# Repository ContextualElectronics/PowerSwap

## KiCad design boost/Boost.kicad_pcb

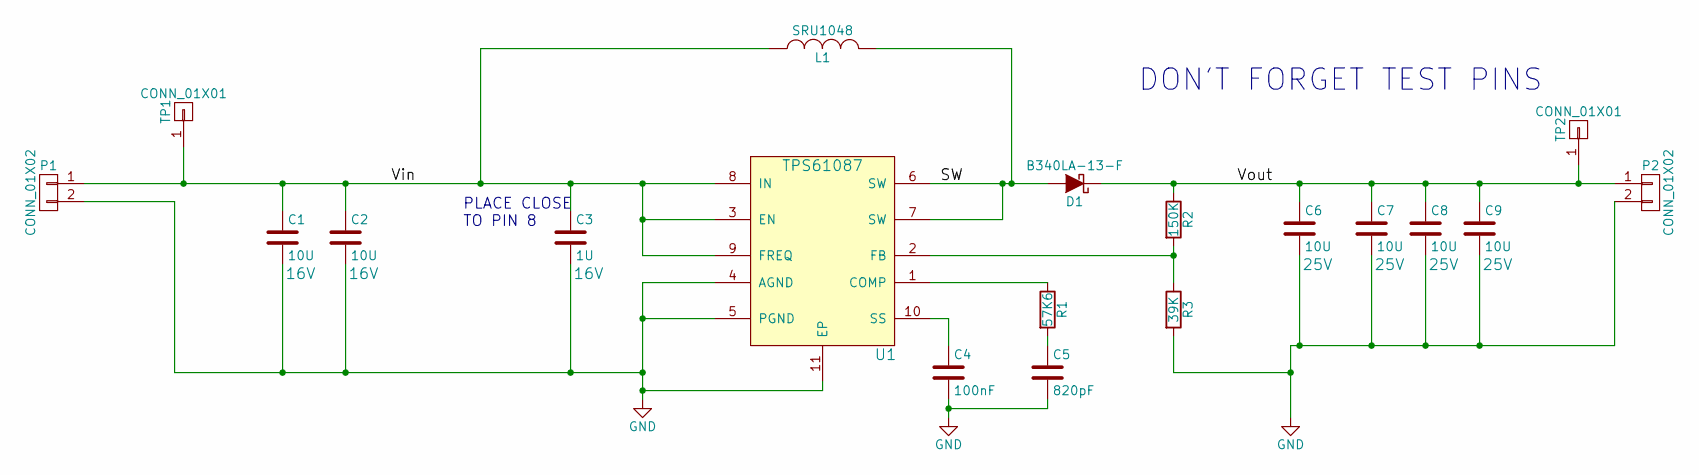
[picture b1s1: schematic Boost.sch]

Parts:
C1, C2: 10U; C_1206_HandSoldering; Voltage 16V
C3: 1U; C_0805_HandSoldering; Voltage 16V
C4: 100nF; C_0805_HandSoldering
C5: 820pF; C_0805_HandSoldering
C6, C7, C8, C9: 10U; C_1206_HandSoldering; Voltage 25V
D1: B340LA-13-F; SMA-SMB_Universal_Handsoldering; MPN B340LA-13-F
L1: SRU1048; MPN SRU1048-4R7Y
P1, P2: CONN_01X02; Pin_Header_Straight_1x02
R1: 57K6; R_0805_HandSoldering
R2: 150K; R_0805_HandSoldering
R3: 39K; R_0805_HandSoldering
TP1, TP2: CONN_01X01; Measurement_Point_Square-SMD-Pad_Big
U1: TPS61087; MPN TPS61087QDRCRQ1

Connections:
/SW: D1.2 (A), L1.2, U1.6 (SW), U1.7 (SW)
/Vin: C1.1, C2.1, C3.1, L1.1, P1.1, TP1.1, U1.3 (EN), U1.8 (IN), U1.9 (FREQ)
/Vout: C6.1, C7.1, C8.1, C9.1, D1.1 (K), P2.1, R2.1, TP2.1; also elsewhere on the board
GND: C1.2, C2.2, C3.2, C4.2, C5.2, C6.2, C7.2, C8.2, C9.2, P1.2, P2.2, R3.2, U1.4 (AGND), U1.5 (PGND), U1.11 (EP); also elsewhere on the board
unnamed: C4.1, U1.10 (SS)
unnamed: C5.1, R1.2
unnamed: R1.1, U1.1 (COMP)
unnamed: R2.2, R3.1, U1.2 (FB)

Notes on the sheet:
PLACE CLOSE TO PIN 8
DON'T FORGET TEST PINS

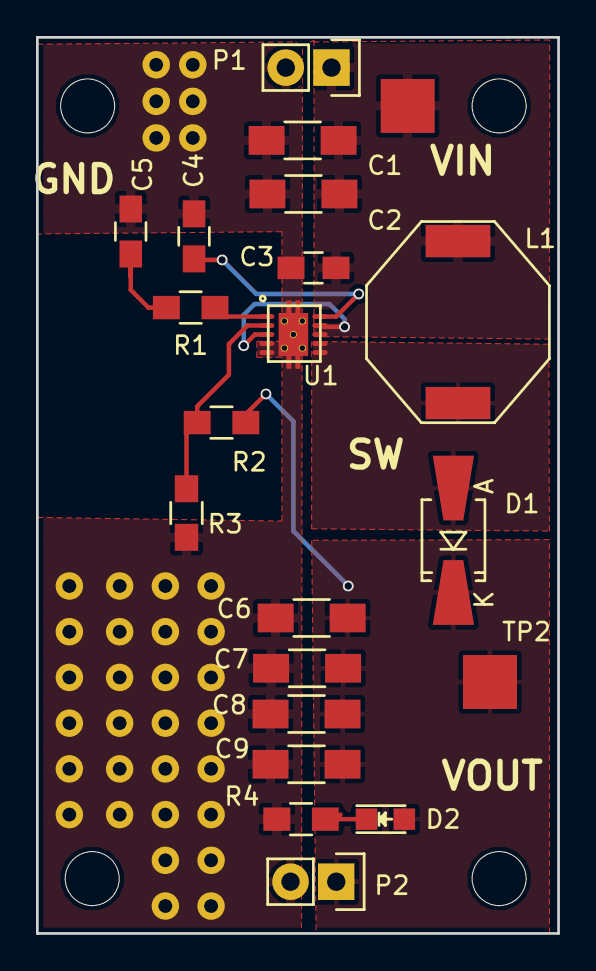
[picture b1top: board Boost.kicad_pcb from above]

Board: 2 copper layers, 29.0 x 49.8 mm, 21 parts (0 on the bottom side), 9 nets.

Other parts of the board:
D2: LED; LED-0805
R4: 500; R_0805_HandSoldering

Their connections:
/Vout: D2.2; also elsewhere on the board
GND: R4.2; also elsewhere on the board
unnamed: D2.1, R4.1

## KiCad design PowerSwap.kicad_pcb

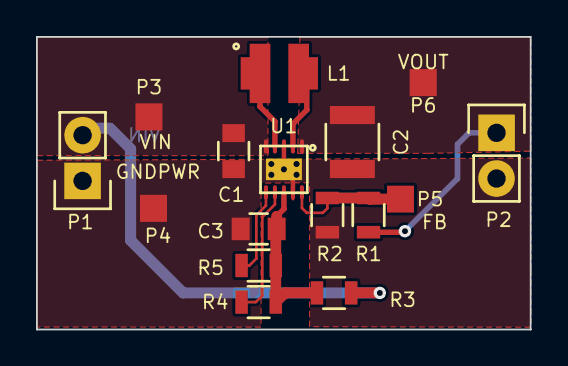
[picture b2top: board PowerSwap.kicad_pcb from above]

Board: 2 copper layers, 27.4 x 16.3 mm, 16 parts (0 on the bottom side), 9 nets.

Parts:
C1: 4.7UF; C_0805
C2: 22UF; C_1210
C3: 0.1UF; C_0805
L1: 2.2uH; LQH3NPN2R2MM0L
P1, P2: CONN_01X02; Pin_Header_Straight_1x02
P3, P4, P5, P6: TST; Measurement_Point_Square-SMD-Pad_Small
R1: 1.2M; R_0805
R2: 215K; R_0805
R3, R4, R5: 0; R_0805
U1: TPS63030

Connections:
/FB: P5.1, R1.2, R2.1, U1.10
/VIN: C1.1, P1.2, P3.1, R3.2, U1.5
/VINA: C3.1, R3.1, R4.2, R5.2, U1.8
/VOUT: C2.1, P2.1, P6.1, R1.1, U1.1
GNDPWR: C1.2, C2.2, C3.2, P1.1, P2.2, P4.1, R2.2, U1.3, U1.9, U1.11
unnamed: L1.1, U1.4
unnamed: L1.2, U1.2
unnamed: R4.1, U1.7
unnamed: R5.1, U1.6

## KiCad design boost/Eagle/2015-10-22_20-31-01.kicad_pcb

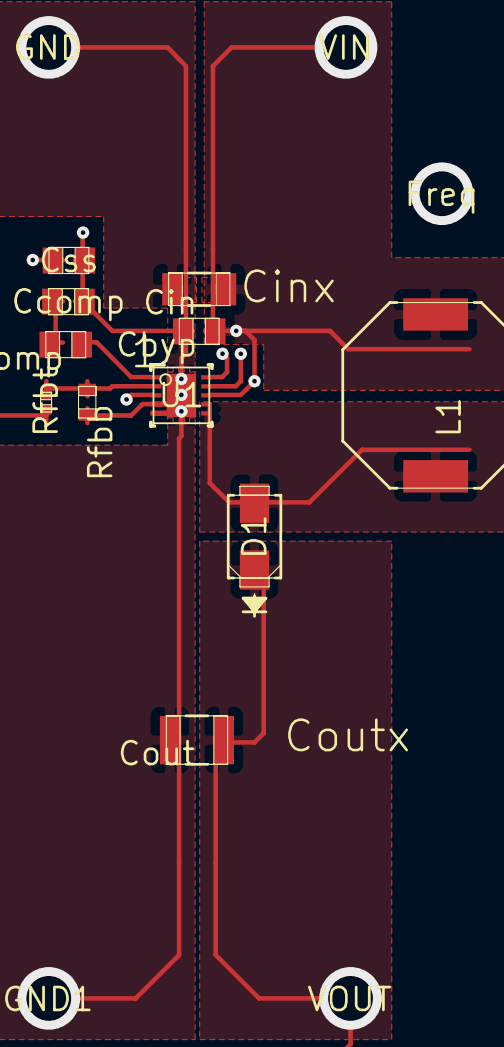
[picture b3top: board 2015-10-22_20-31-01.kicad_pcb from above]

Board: 10 copper layers, 16 parts (0 on the bottom side), 9 nets.

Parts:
Cbyp: 0805
Ccomp: 0805
Cin: 1206
Cout: 1210
Css: 0805
D1: SMA
Freq: TP-1502
GND, GND1: TP-1502
L1: SRU1048
Rcomp: 0805
Rfbb: 0603
Rfbt: 0402
U1: DRC0010A
VIN: TP-1502
VOUT: TP-1502

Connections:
0: Cbyp.2, Ccomp.2, Cin.2, Cout.2, Css.2, GND.1, GND1.1, Rfbb.2, U1.4, U1.5, U1.11
1: Cbyp.1, Cin.1, L1.1, U1.3, U1.8, VIN.1
2: Cout.1, D1.1, Rfbt.1, VOUT.1
4: D1.2, L1.2, U1.6, U1.7
5: Rcomp.1, U1.1
6: Rfbb.1, Rfbt.2, U1.2
7: Ccomp.1, Rcomp.2
13: Freq.1, U1.9
14: Css.1, U1.10

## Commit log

2015-08-01 Added TPS63030 component plus passives
2015-08-09 Added values to schematic and added inductor footprint
2015-08-09 Added TPS63030 Footprint
2015-08-09 Imported footprints
2015-08-10 Finished Power Swap Layout
2015-08-13 Added via stitching and generated gerbers for fabrication
2015-10-23 Moved previous design to buck-boost folder, created boost folder
2015-10-23 Added BOM and EAGLE layout from web bench
2015-10-29 Added components as shown in example schematic on TPS61087 datasheet
2015-11-02 Added footprints to layout
2015-11-04 Updated component values
2015-11-04 Added EAGLE files from WebBench output
2015-11-04 Initial Layout
2015-11-05 Finished layout
2015-11-08 Added indicator LED, mounting holes and a logo.
2015-11-08 Gerber generation for Rev 1 proto
